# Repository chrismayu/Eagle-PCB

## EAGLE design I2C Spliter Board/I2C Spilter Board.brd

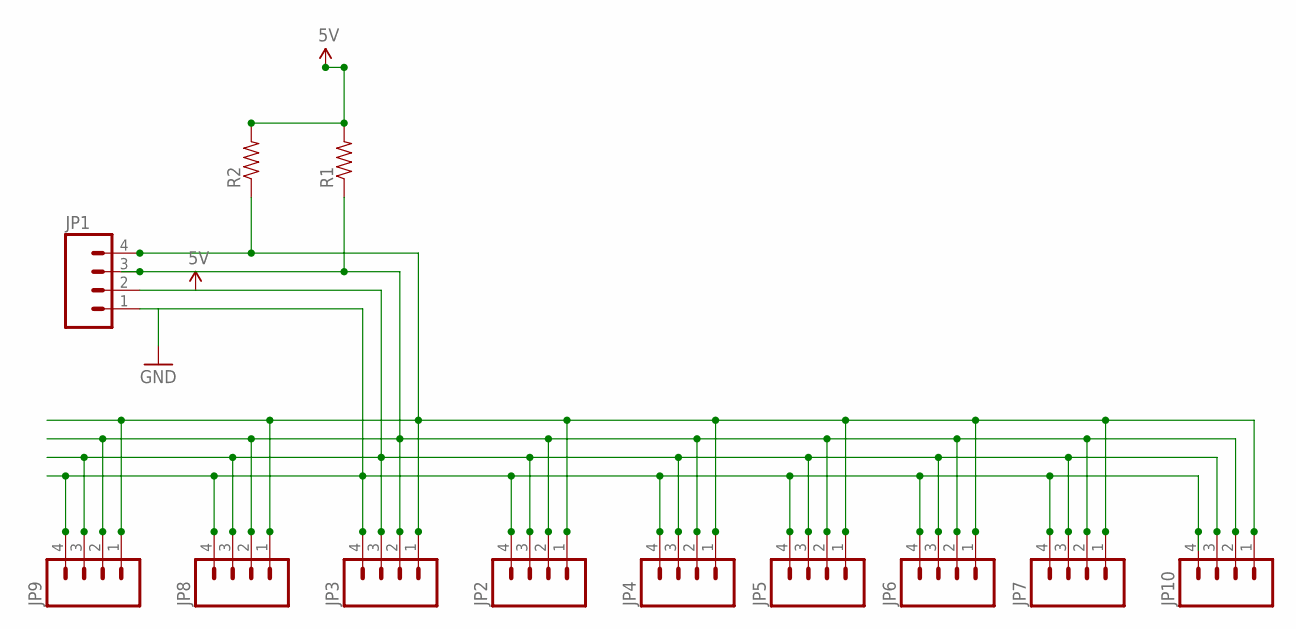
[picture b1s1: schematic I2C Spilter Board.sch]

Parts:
JP1, JP2, JP3, JP4, JP5, JP6, JP7, JP8, JP9, JP10: M04PTH; 1X04
R1, R2: RESISTORAXIAL-0.3; AXIAL-0.3

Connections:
5V: JP1.2, JP2.3, JP3.3, JP4.3, JP5.3, JP6.3, JP7.3, JP8.3, JP9.3, JP10.3, R1.P$2 (2), R2.P$2 (2)
GND: JP1.1, JP2.4, JP3.4, JP4.4, JP5.4, JP6.4, JP7.4, JP8.4, JP9.4, JP10.4
unnamed: JP1.3, JP2.2, JP3.2, JP4.2, JP5.2, JP6.2, JP7.2, JP8.2, JP9.2, JP10.2, R1.P$1 (1)
unnamed: JP1.4, JP2.1, JP3.1, JP4.1, JP5.1, JP6.1, JP7.1, JP8.1, JP9.1, JP10.1, R2.P$1 (1)

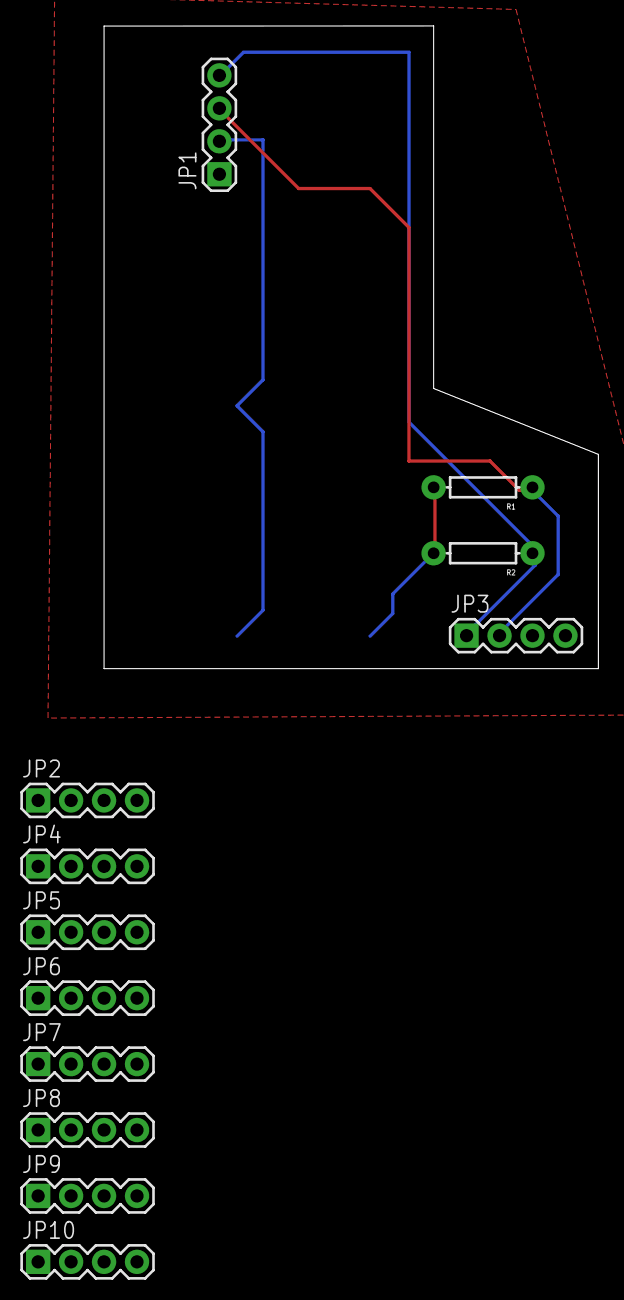
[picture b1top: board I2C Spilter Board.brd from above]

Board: 2 copper layers, 38.1 x 49.5 mm, 12 parts (0 on the bottom side), 4 nets.

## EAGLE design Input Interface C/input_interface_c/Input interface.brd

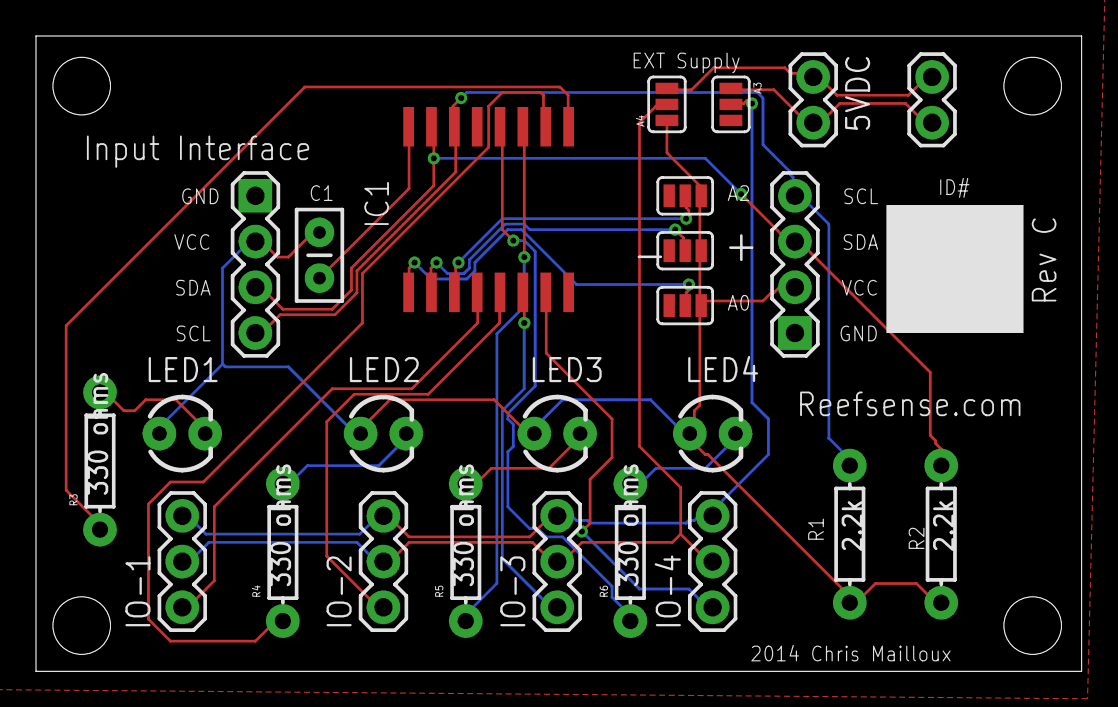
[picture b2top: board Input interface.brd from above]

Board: 2 copper layers, 58.1 x 35.3 mm, 25 parts (0 on the bottom side), 24 nets.

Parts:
5VDC, 5VDC1: +; 1X02
A0, A1, A2, A3, A4: SJ_3
C1: CAP-PTH-SMALL2
IC1: PCF8574T; SO16W
IO-1, IO-2, IO-3, IO-4: 1X03
JP1, JP2: 1X04
LED1, LED2, LED3, LED4: LED3MM
R1, R2: 2.2k; AXIAL-0.3
R3, R4, R5, R6: 330 ohms; AXIAL-0.3

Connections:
5V: A0.3, A1.3, A2.3, A4.1, C1.1, JP1.2, JP2.2, LED1.A, LED2.A, LED3.A, LED4.A, R1.P$2, R2.P$2
GND: A0.1, A1.1, A2.1, A3.3, IC1.8, JP1.1, JP2.1
unnamed: IC1.4, IO-1.1
unnamed: IC1.5, IO-2.1
unnamed: IC1.6, IO-3.1
unnamed: A0.2, IC1.1
unnamed: IC1.14, JP1.4, JP2.4, R1.P$1
unnamed: IC1.15, JP1.3, JP2.3, R2.P$1
unnamed: A1.2, IC1.2
unnamed: C1.2, IC1.16
unnamed: A2.2, IC1.3
unnamed: IC1.7, IO-4.1
unnamed: IC1.9, R3.P$1
unnamed: IC1.10, R4.P$1
unnamed: IC1.11, R5.P$1
unnamed: IC1.12, R6.P$1
unnamed: LED1.K, R3.P$2
unnamed: LED2.K, R4.P$2
unnamed: LED3.K, R5.P$2
unnamed: LED4.K, R6.P$2
unnamed: A4.2, IO-1.2, IO-2.2, IO-3.2, IO-4.2
unnamed: 5VDC.1, 5VDC1.1, A4.3
unnamed: 5VDC.2, 5VDC1.2, A3.1
unnamed: A3.2, IO-1.3, IO-2.3, IO-3.3, IO-4.3

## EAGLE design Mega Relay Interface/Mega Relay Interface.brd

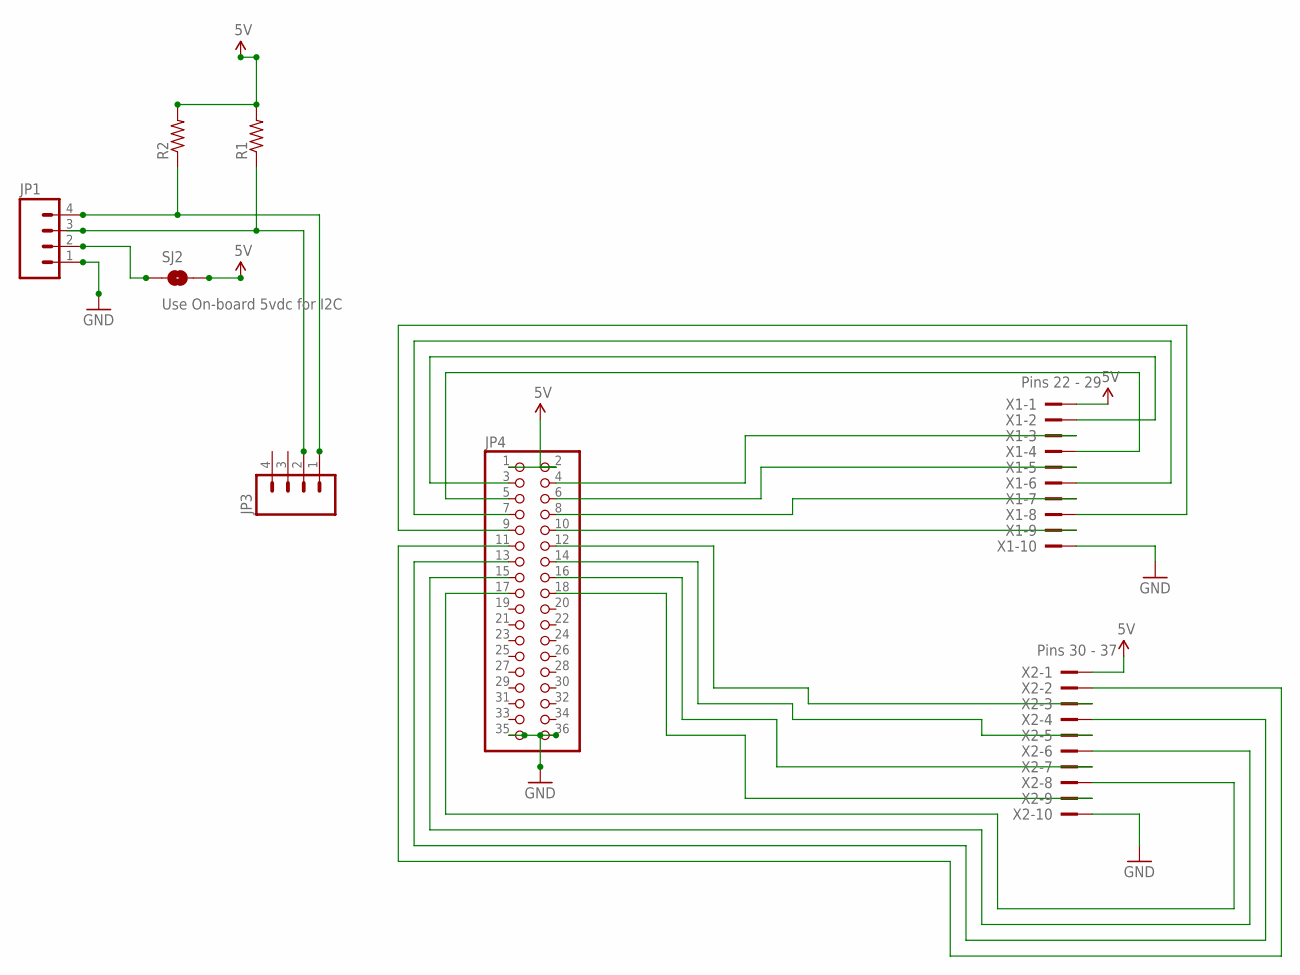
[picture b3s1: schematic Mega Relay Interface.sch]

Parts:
JP1, JP3: M04PTH; 1X04
JP4: PINHD-2X18; 2X18
R1, R2: RESISTORAXIAL-0.3; AXIAL-0.3
SJ2: Use On-board 5vdc for I2C; SJ_2S
X1: Pins 22 - 29; PAK100/2500-10
X2: Pins 30 - 37; PAK100/2500-10

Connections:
5V: JP4.1, JP4.2, R1.P$2 (2), R2.P$2 (2), SJ2.2, X1.1, X2.1
GND: JP1.1, JP4.35, JP4.36, X1.10, X2.10
unnamed: JP4.3, X1.2
unnamed: JP4.4, X1.3
unnamed: JP4.5, X1.4
unnamed: JP4.7, X1.6
unnamed: JP4.6, X1.5
unnamed: JP4.9, X1.8
unnamed: JP4.8, X1.7
unnamed: JP4.11, X2.2
unnamed: JP4.10, X1.9
unnamed: JP4.12, X2.3
unnamed: JP4.14, X2.5
unnamed: JP4.16, X2.7
unnamed: JP4.18, X2.9
unnamed: JP1.2, SJ2.1
unnamed: JP4.13, X2.4
unnamed: JP4.15, X2.6
unnamed: JP4.17, X2.8
unnamed: JP1.3, JP3.2, R1.P$1 (1)
unnamed: JP1.4, JP3.1, R2.P$1 (1)

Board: 2 copper layers, 8 parts (0 on the bottom side), 21 nets, no tracks yet.

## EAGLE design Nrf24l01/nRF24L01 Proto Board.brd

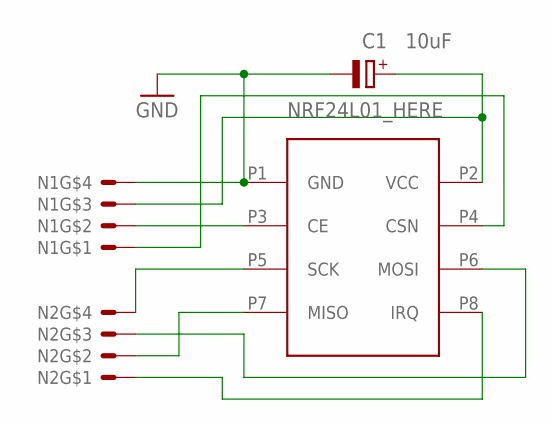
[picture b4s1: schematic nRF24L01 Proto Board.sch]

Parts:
C1: 10uF; E2,5-6
N1, N2: 4PINHEADER_S
NRF24L01_HERE: NRF24L01A; NRF24L01

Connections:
GND: C1.-, N1.N3, NRF24L01_HERE.P1 (GND)
unnamed: N1.N0, NRF24L01_HERE.P4 (CSN)
unnamed: N1.N1, NRF24L01_HERE.P3 (CE)
unnamed: N2.N3, NRF24L01_HERE.P5 (SCK)
unnamed: N2.N2, NRF24L01_HERE.P6 (MOSI)
unnamed: C1.+, N1.N2, NRF24L01_HERE.P2 (VCC)
unnamed: N2.N1, NRF24L01_HERE.P7 (MISO)
unnamed: N2.N0, NRF24L01_HERE.P8 (IRQ)

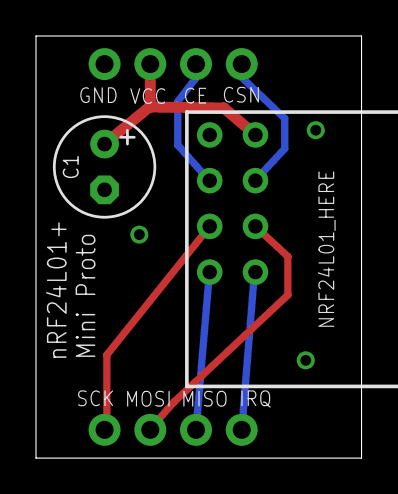
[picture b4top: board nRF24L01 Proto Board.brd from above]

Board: 2 copper layers, 18.1 x 23.4 mm, 4 parts (0 on the bottom side), 8 nets.

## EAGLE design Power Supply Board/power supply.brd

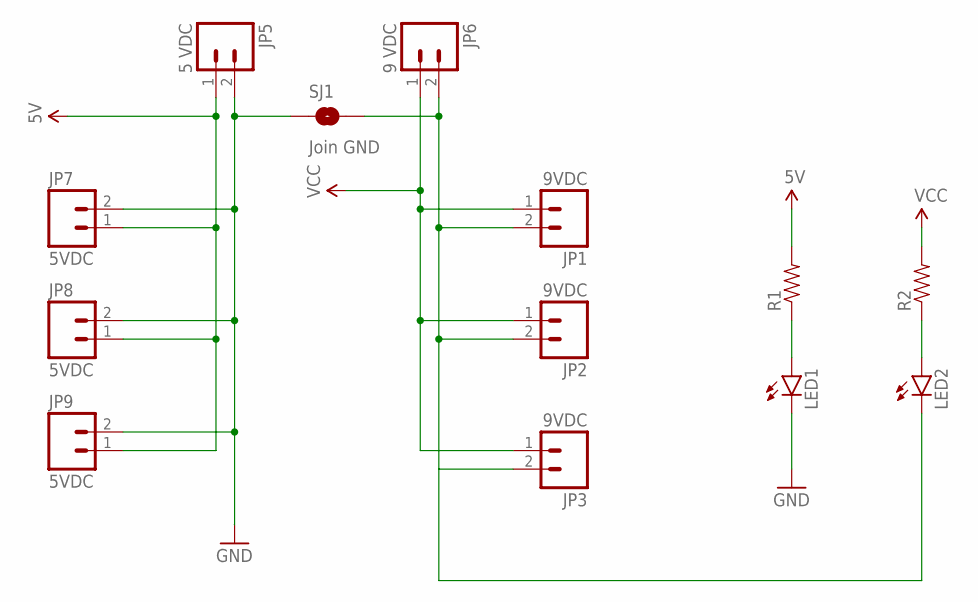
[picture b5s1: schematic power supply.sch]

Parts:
JP1, JP2, JP3: 9VDC; 1X02
JP5: 5 VDC; SCREWTERMINAL-5MM-2
JP6: 9 VDC; SCREWTERMINAL-5MM-2
JP7, JP8, JP9: 5VDC; 1X02
LED1, LED2: LED3MM
R1, R2: RESISTORAXIAL-0.3; AXIAL-0.3
SJ1: Join GND; SJ_2S-NO

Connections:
5V: JP5.1, JP7.1, JP8.1, JP9.1, R1.P$2 (2)
GND: JP5.2, JP7.2, JP8.2, JP9.2, LED1.K (C), SJ1.1
unnamed: LED1.A, R1.P$1 (1)
unnamed: LED2.A, R2.P$1 (1)
unnamed: JP1.2, JP2.2, JP3.2, JP6.2, LED2.K (C), SJ1.2
VCC: JP1.1, JP2.1, JP3.1, JP6.1, R2.P$2 (2)

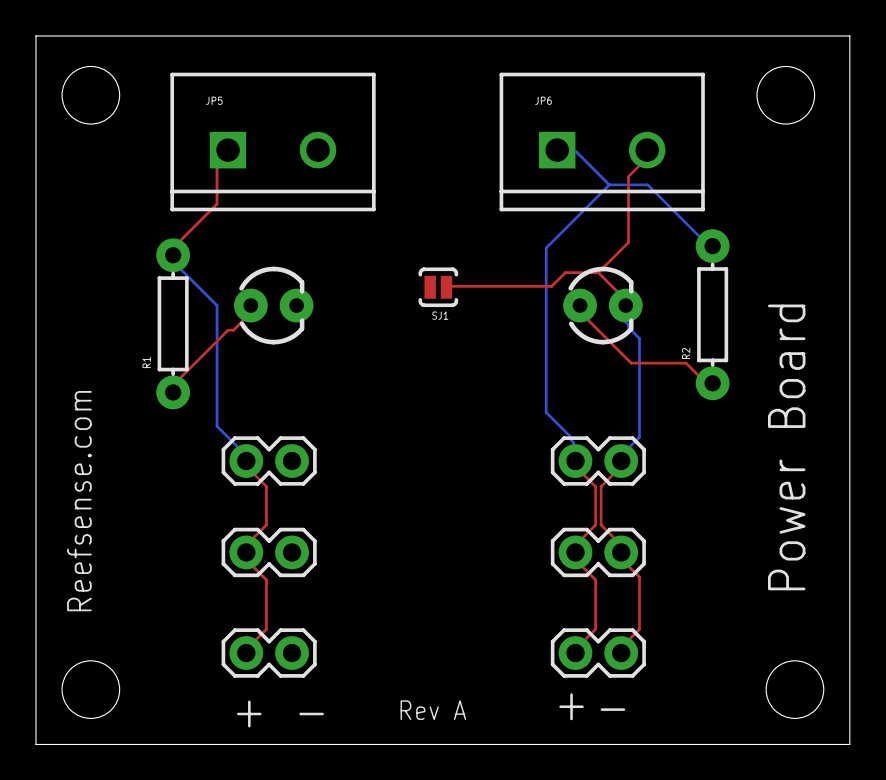
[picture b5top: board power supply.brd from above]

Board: 2 copper layers, 45.2 x 39.4 mm, 13 parts (0 on the bottom side), 6 nets.

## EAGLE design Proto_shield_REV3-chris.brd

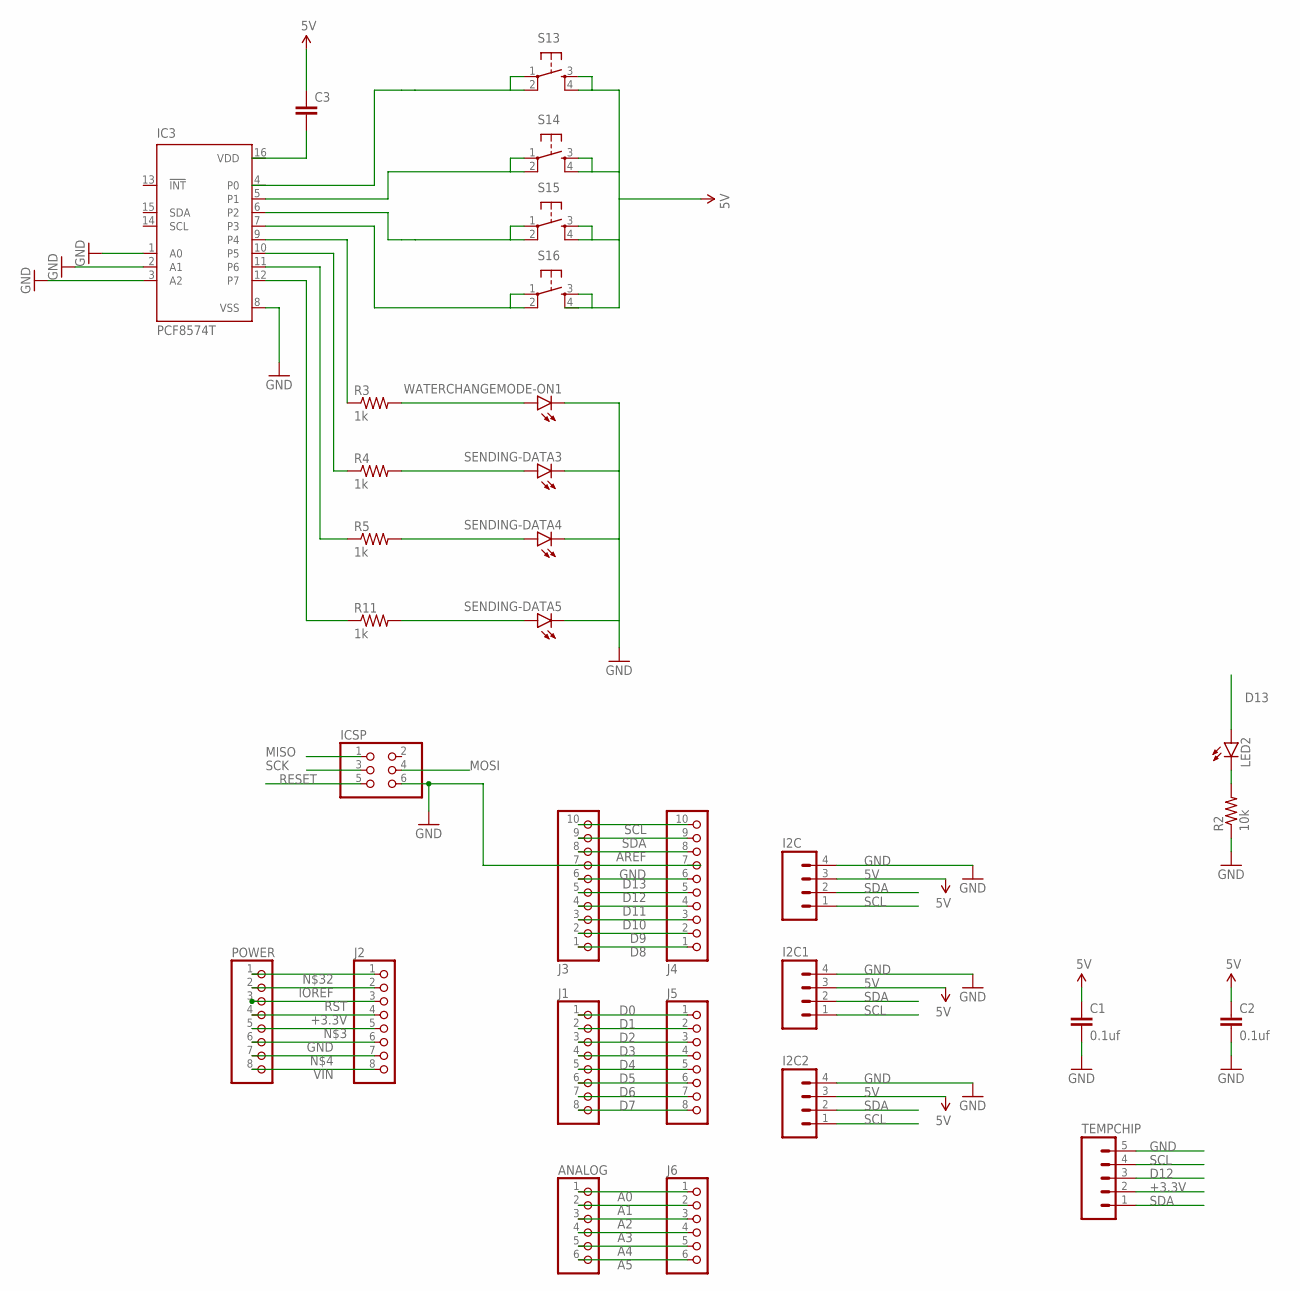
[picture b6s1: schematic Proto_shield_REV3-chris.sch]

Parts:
ANALOG: PINHD-1X6; 1X06
C1, C2: 0.1uf; CAP-PTH-SMALL2
C3: CAPPTH2; CAP-PTH-SMALL2
I2C, I2C1, I2C2: M04PTH; 1X04
IC3: PCF8574T; SO16W
ICSP: PINHD-2X3; 2X03
J1, J2, J5: PINHD-1X8TH; 1X08-TH
J3, J4: PINHD-1X10TH; 1X10-TH
J6: PINHD-1X6; 1X06
LED2: LED5MM
POWER: PINHD-1X8TH; 1X08-TH
R2: 10k; AXIAL-0.3
R3, R4, R5, R11: 1k; AXIAL-0.3
S13, S14, S15, S16: TAC_SWITCHPTH; TACTILE-PTH
SENDING-DATA3, SENDING-DATA4, SENDING-DATA5: LED3MM
TEMPCHIP: M051.27MM; 1X05-1.27MM
WATERCHANGEMODE-ON1: LED3MM

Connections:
5V: C1.1, C2.1, C3.1, I2C.3, I2C1.3, I2C2.3, S13.3, S13.4, S14.3, S14.4, S15.3, S15.4, S16.3, S16.4
+3.3V: J2.4, POWER.4, TEMPCHIP.2
A0: ANALOG.1, J6.1
A1: ANALOG.2, J6.2
A2: ANALOG.3, J6.3
A3: ANALOG.4, J6.4
A4: ANALOG.5, J6.5
A5: ANALOG.6, J6.6
AREF: J3.8, J4.8
D0: J1.1, J5.1
D1: J1.2, J5.2
D2: J1.3, J5.3
D3: J1.4, J5.4
D4: J1.5, J5.5
D5: J1.6, J5.6
D6: J1.7, J5.7
D7: J1.8, J5.8
D8: J3.1, J4.1
D9: J3.2, J4.2
D10: J3.3, J4.3
D11: J3.4, J4.4
D12: J3.5, J4.5, TEMPCHIP.3
D13: J3.6, J4.6, LED2.A
GND: C1.2, C2.2, I2C.4, I2C1.4, I2C2.4, IC3.1 (A0), IC3.2 (A1), IC3.3 (A2), IC3.8 (VSS), ICSP.6, J2.6, POWER.6, R2.P$1 (1), SENDING-DATA3.K (C), SENDING-DATA4.K (C), SENDING-DATA5.K (C), TEMPCHIP.5, WATERCHANGEMODE-ON1.K (C)
IOREF: J2.2, POWER.2
MISO: ICSP.1
MOSI: ICSP.4
unnamed: LED2.K (C), R2.P$2 (2)
unnamed: J2.5, POWER.5
unnamed: J2.7, POWER.7
unnamed: R5.P$2 (2), SENDING-DATA4.A
unnamed: R11.P$2 (2), SENDING-DATA5.A
unnamed: R3.P$2 (2), WATERCHANGEMODE-ON1.A
unnamed: IC3.11 (P6), R5.P$1 (1)
unnamed: IC3.12 (P7), R11.P$1 (1)
unnamed: IC3.9 (P4), R3.P$1 (1)
unnamed: IC3.10 (P5), R4.P$1 (1)
unnamed: IC3.7 (P3), S16.1, S16.2
unnamed: IC3.5 (P1), S14.1, S14.2
unnamed: J2.1, POWER.1
unnamed: S13.1, S13.2
unnamed: IC3.6 (P2), S15.1, S15.2
unnamed: R4.P$2 (2), SENDING-DATA3.A
RESET: ICSP.5
RST: J2.3, POWER.3
SCK: ICSP.3
SCL: I2C.1, I2C1.1, I2C2.1, J3.10, J4.10, TEMPCHIP.4
SDA: I2C.2, I2C1.2, I2C2.2, J3.9, J4.9, TEMPCHIP.1
VDD: IC3.16 (VDD)
VIN: J2.8, POWER.8

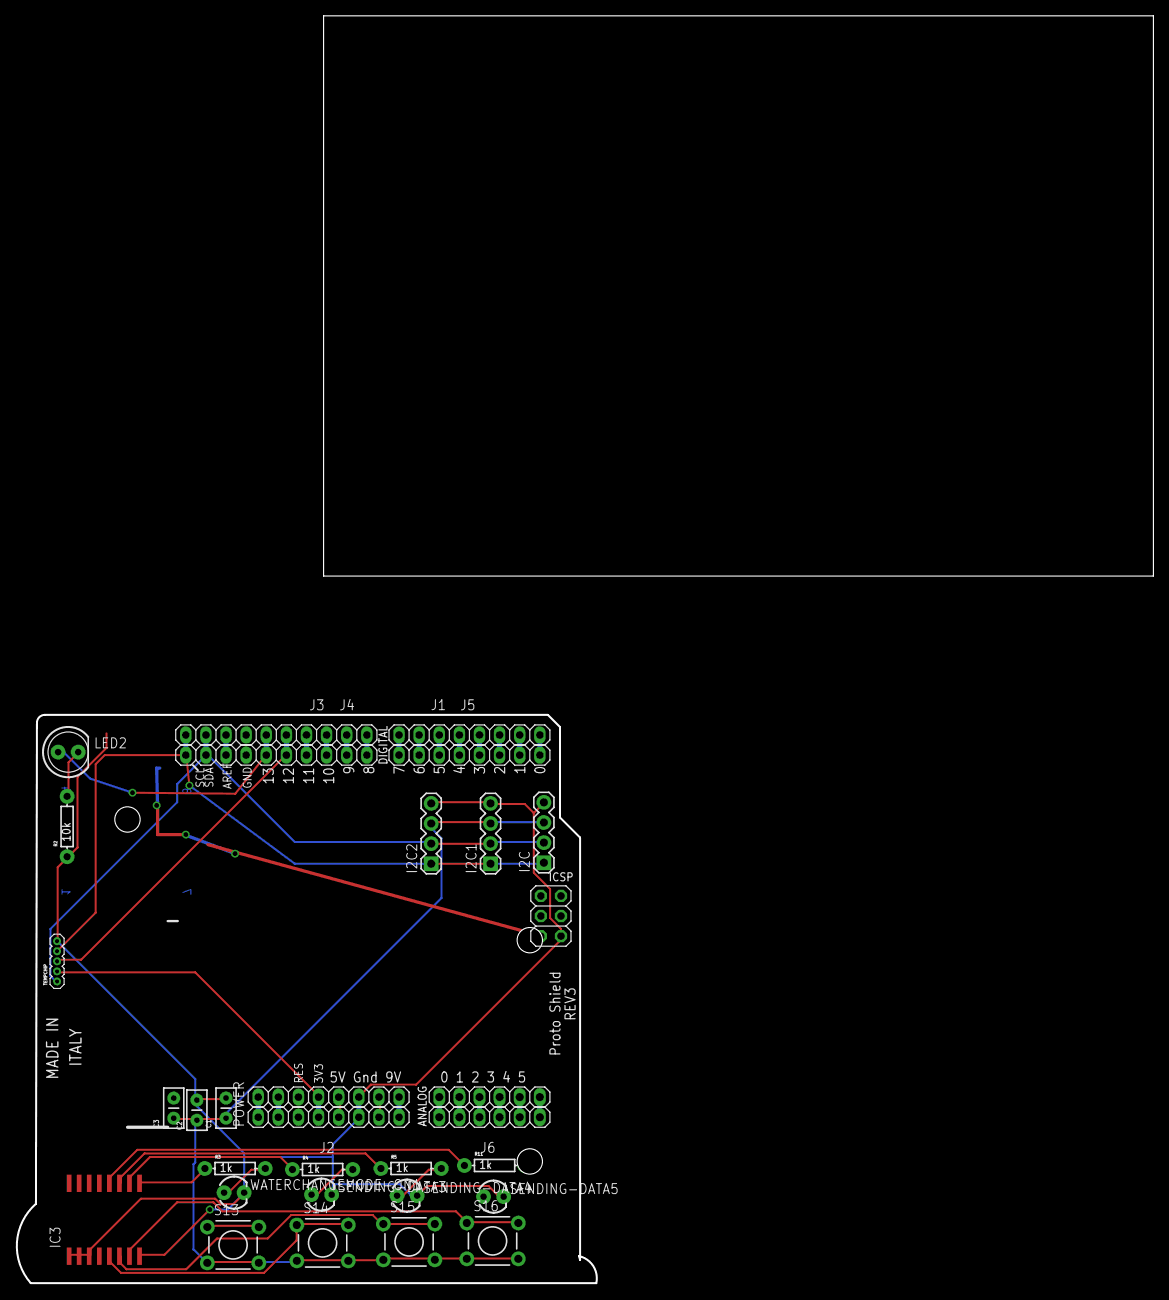
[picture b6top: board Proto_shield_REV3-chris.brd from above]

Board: 2 copper layers, 73.2 x 71.8 mm, 31 parts (0 on the bottom side), 45 nets.

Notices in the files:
parts and their libraries:
SparkFun-Connectors: Licensing: Creative Commons ShareAlike 4.0 International - https://creativecommons.org/licenses/by-sa/4.0
